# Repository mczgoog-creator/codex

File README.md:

# DRV8701 双电机驱动板 · Rev B

**12 V、39×60 mm、4 层、1.6 mm** 双电机驱动板。Rev B 重新安排了两路半桥、去耦和功率回路，并加入 TPS25910 主电源控制。每段线路、过孔和铜区均按明确坐标人工规划，未使用自动布线或路径搜索。

[网页端 KiCad 导入包](downloads/DRV8701_12V_KiCad5_Import.zip) · [完整工程和资料 ZIP](downloads/DRV8701_12V_EasyEDA_Pro.zip) · [工程说明](hardware/drv8701-dual-12v/README.md)

## 在嘉立创 EDA 专业版中打开

网页端请下载 **`DRV8701_12V_KiCad5_Import.zip`**，在开始页选择 **「导入 KiCad」**，直接选择 ZIP。按[官网指引](https://prodocs.lceda.cn/cn/import-export/import-kicad/index.html)，导入副本采用真实 KiCad 5.1 格式，并通过 KiCad 自带归档功能打包。步骤和导入后检查见[网页导入说明](hardware/drv8701-dual-12v/IMPORT_IN_WEB_PRO.md)。

原始 KiCad 9 工程和自带库也随包保存。`EasyEDA_Pro/DRV8701_DUAL_12V.eprj3` 是另供 V4.1+ 离线／半离线桌面客户端使用的文件夹工程；需保留整个目录，不能当作网页 `.epro` 文件导入。

## 本版变化

- 四组高边源极与低边漏极相邻，通过局部宽铜连接相节点；功率转层采用四孔阵列。公共供电在 C15 正极处汇合并向两路分配。
- 泵和内部电源去耦至芯片的关键连接留在顶层；VM 先到 C3/C10，再到芯片 VM 脚。SH 源参考采用独立细线返回高边源极焊盘。
- 新增 U6 TPS25910、SW1 和五个配套无源件。SW1 控制主电源，原 U5 继续控制 DRV8701 的 nSLEEP。原 38 个元件的取值保留；原有脚网络仅 P2.1 从 VM 改为新增电源入口 VM_RAW。

主电源连续额定 5 A，R12=40.2 kΩ 对应手册限流 4.5–5.5 A。主开关关闭时芯片仍消耗约 2.5 mA 典型／4 mA 最大，分压另约 90 µA；不提供电池物理隔离或反向电流阻断。开启主电源前应保持两路桥关闭，VM 稳定后再使能，详见[首次上电步骤](hardware/drv8701-dual-12v/FIRST_POWER_ON.md)。

## 文件与检查边界

- [原理图 PDF](hardware/drv8701-dual-12v/DRV8701_DUAL_12V_schematic.pdf)、[PCB 各层检查图](hardware/drv8701-dual-12v/PCB_layers_review.pdf)
- [元件清单](hardware/drv8701-dual-12v/components.csv)、[采购约束](hardware/drv8701-dual-12v/procurement_notes.csv)
- [布局与电流路径说明](hardware/drv8701-dual-12v/source/engineering_review.md)、[主电源手册核对](hardware/drv8701-dual-12v/source/tps25910_power_control_review.md)
- [原图保留范围核对](hardware/drv8701-dual-12v/validation/rev_b_original_source_contract.json)、[交付检查记录](hardware/drv8701-dual-12v/validation/final_delivery.json)
- [独立布局几何检查](hardware/drv8701-dual-12v/validation/layout_geometry_audit.json)、[最后丝印与铜线复核](hardware/drv8701-dual-12v/validation/rev_b_final_silk_cleanup.json)、[Rev B 工程审计](hardware/drv8701-dual-12v/validation/rev_b_engineering_audit.json)

Rev B 共 **45 个元件、38 个网络、203 个唯一物理引脚／211 个焊盘实例、592 段线路、151 个过孔、12 个铜区**。冻结后的 KiCad 9 源板 **DRC 0 违规／0 未连接，原理图 ERC 0 错误／0 警告**。独立几何检查通过：14 条关键去耦连接均在顶层，最长 2.9713 mm；丝印与焊盘／过孔碰撞为 0，审核范围内的直角／锐角弯折为 0。

网页导入副本已通过真实 **KiCad 5.1.9：ERC 0 错误／0 警告，PCB DRC 0 错误／0 未连接**；45 个元件、38 网、203 脚逐值逐脚一致。PCB 检查已重填全部铜区并检查走线与填铜。副本的 624 段线路中，新增 32 段完全位于原 MOS 漏极焊盘铜内，新增实际铜面积为 0；原 592 段线路、151 孔、211 焊盘及 12 铜区保留。见[旧版最终等价核对](hardware/drv8701-dual-12v/validation/legacy5_final_pcb_equivalence.json)。

源软件检查不替代专业版实际导入检查。弯折统计排除同网焊盘／过孔内部和真实分支结点，具体范围见几何报告。五页 PCB 检查图、分层 PDF 及顶／底 SVG／PNG 均按冻结源板重新导出，来源 SHA 见[预览导出记录](hardware/drv8701-dual-12v/validation/preview_exports.json)。

桌面原生工程的[静态转换审计](hardware/drv8701-dual-12v/EasyEDA_Pro/native-final-audit.json) 已通过：元件／引脚／线路／过孔及 12 个填充铜区均与冻结源板对应，官方工程结构检查 0 错误／0 警告。未运行真实专业版桌面客户端，网页用户仍使用上面的 KiCad 导入 ZIP。

**真实嘉立创网页导入／DRC、样板通电和温升测试尚未完成。** 导入会重新铺铜，需复核四层各 35 µm 铜、功率铜区和规则。原图的 100 nF 电荷泵／内部电源去耦、较弱齐纳供电、IDRIVE 设置和无 GND 的控制插座仍保留，并在工程说明中列出。MOS 原厂手册已读取，采购需匹配普通 SOP Advance 封装；手册没有提供推荐 PCB 焊盘图。

## 来源与许可证

官方开源转换／校验工具保留各自的 Apache-2.0／MIT 许可证；上游地址与精确版本见[版本记录](hardware/drv8701-dual-12v/tools/easyeda-native/upstream-versions.json)。这些工具许可证不自动覆盖电路设计、第三方封装或厂商 PDF。原图、封装和手册来源见工程说明。

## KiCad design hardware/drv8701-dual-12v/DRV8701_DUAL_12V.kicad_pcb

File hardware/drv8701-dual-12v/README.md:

# DRV8701 双电机驱动板 · Rev B · 12 V

依据用户原始《8701驱动板（无电流检测2.0）.pdf》重建。本版重新安排半桥功率器件、去耦、供电和回流，并按用户后续要求加入主电源控制。**原 38 个元件的取值全部保留；原有引脚唯一授权网络变化是 P2.1 从 VM 改接 VM_RAW。** 原图其余连接保留，新增七件：U6、SW1、R10–R12、C18、C19。核对见 [rev_b_original_source_contract.json](validation/rev_b_original_source_contract.json)。

PCB 每个元件位置、线路、过孔和铜区边界均人工规划，未使用嘉立创自动布线器、其它自动布线器或路径搜索。脚本按明确坐标生成线路；铺铜填充只是按既定边界生成铜区。

## 打开工程与交付文件

用户使用嘉立创 EDA 专业版**网页端**。主要入口为 **`DRV8701_12V_KiCad5_Import.zip`**：在网页开始页选择 **「导入 KiCad」**后直接选择 ZIP。依据[官网指引](https://prodocs.lceda.cn/cn/import-export/import-kicad/index.html)，导入副本采用真实 KiCad 5.1 格式并由 KiCad 自带归档功能打包。步骤见 [IMPORT_IN_WEB_PRO.md](IMPORT_IN_WEB_PRO.md)。

原始 KiCad 9 源文件与库保留。桌面入口 `EasyEDA_Pro/DRV8701_DUAL_12V.eprj3` 由官方转换器及独立后处理生成，另供专业版 V4.1+ 离线／半离线客户端使用，需保留整个目录；不能当作网页 `.epro` 文件导入。

**尚未在真实嘉立创 EDA 专业版完成导入和 DRC。** 导入会重建铜区，需复核板框、叠层、功率铜区和设计规则。桌面文件的 schema／真实导出模板单位差异见 `tools/easyeda-native/RESEARCH.md`；首次打开应确认实际尺寸和规则值。

|文件|用途|
|---|---|
|`DRV8701_DUAL_12V.kicad_sch/.kicad_pcb/.kicad_pro`|Rev B 可编辑原理图、PCB、规则|
|`DRV8701_Custom.kicad_sym`、`DRV8701_Custom.pretty/`|本地符号及封装；配套库表同目录保存|
|`KiCad_Import_5/`|真实 KiCad 5.1 格式的网页导入副本|
|`imports/DRV8701_12V_KiCad5_Import.zip`|专用网页导入 ZIP|
|`EasyEDA_Pro/`|另供新版桌面客户端使用的文件夹原生工程|
|`DRV8701_DUAL_12V_schematic.pdf`|原理图阅读版|
|`PCB_layers_review.pdf`、`pcb_top/bottom.svg/.png`|从源 CAD 导出的各层检查图与顶底预览；底层 PNG/SVG 已镜像，按从底面观察显示|
|`components.csv`、`procurement_notes.csv`|元件值、封装及采购额定参数|
|`source/source_netlist.json`|原始 PDF 独立复核网表，作为原图基准保留|
|`validation/rev_b_original_source_contract.json`|原图取值、连接与授权主电源差异核对|
|`final_drc.json`、`validation/schematic_erc.json`|冻结后的 KiCad 9 DRC 与原理图 ERC|
|`validation/layout_geometry_audit.json`|独立读取实际 PCB 的路径、弯折、过孔与丝印检查|
|`validation/rev_b_final_silk_cleanup.json`|最终丝印调整与唯一最后铜线修改范围|
|`validation/rev_b_engineering_audit.json`|本版功率网络、填铜与工程审计|
|`validation/preview_exports.json`|本版预览与各层 PDF 的源板 SHA／导出记录|
|`source/engineering_review.md`|本版布局与电流路径说明|
|`source/tps25910_power_control_review.md`|主电源芯片手册、启动／限流／关闭状态核对|
|`FIRST_POWER_ON.md`|首次上电和两级开关操作步骤|
|`footprint_geometry.json`、`manual_routes.json`|封装依据及人工规划线路记录|
|`scripts/generate_schematic.py`、`tools/build_board.py`|原理图及明确坐标的 PCB 生成程序|
|`validation/`|本版最终检查记录|

用 KiCad 9 打开 `.kicad_pro` 即可读取同目录库。重建程序会覆盖其负责的设计文件，运行前应保存手工编辑副本。

## 尺寸、电流与布局

仅采用用户电机表格的 **12 V** 条件：每路较高档额定 0.4 A、堵转 1.8 A；电机路径按每路 1.8 A，公共供电／回流按合计 3.6 A 规划。堵转值用于短时最大电流初筛，不表示允许持续堵转。

本版 **39×60 mm、4 层、标称 1.6 mm**，元件全在顶面。四铜层均 **35 µm（1 oz）**，孔电阻计算假设成品孔铜至少 20 µm。名义叠层：两面阻焊各 0.01 mm、四铜层各 0.035 mm、两段半固化片各 0.20 mm、中芯板 1.04 mm，总厚 1.60 mm；板厂应据实际材料匹配成品规格。普通 R/C/LED 为 0603，R8/R9 为 1210，新增 C18 为 0805；没有小于 0402 的贴片。

|通路|本版设计|
|---|---|
|P2 至 U6、U6 至 C15 及两路主供电|外层公共主干 1.80 mm；C15 正极为汇合与分配点|
|In2.Cu 并行供电|4.6 mm VM 公共铜带与局部宽铜支路|
|高边 MOS 漏极|短 1.0 mm 外层支路，并由内层铜和四孔阵列连接裸露漏极焊盘|
|高边源极至低边漏极|相邻封装间的局部顶层宽铜，四组半桥均按相同结构安排|
|电机连接器|0.70 mm 外层主线，每个相节点配四孔功率阵列|
|低边 MOS 源极|短支线接本地宽铜，四孔阵列接地；F.Cu／In1.Cu／B.Cu 地铜提供并行回流|
|U6 IN／OUT|各三个并联引脚，每脚短 0.45 mm 连接接入公共铜；不是单根 0.45 mm 线路承担 3.6 A|
|信号与驱动支路|约 0.20–0.30 mm；这些线路不承担电机主电流|

IPC-2221 经验式 `I=k×ΔT^0.44×A^0.725`（A 为平方 mil）用于初筛。35 µm 铜、约 10°C 温升时，外层 1.8 A／3.6 A 线宽约 0.676／1.758 mm，内层约 1.76／4.57 mm，因此内层公共 VM 铜带取 4.6 mm。该经验式不计算实际板上的电流密度、开关波形或温升，成品仍需测量。

C15 安排在受控 VM 供电汇合处，两路从其正极向外分配。每组高／低边 MOS 旋转后令高边源极紧邻低边裸露漏极，以宽铜连接相节点。泵／内部电源去耦至芯片的关键连接留在顶层，VM 电源先进入 C3/C10 再到 VM 引脚；C4/C11 位于功率母线旁。SH 源参考采用独立细线返回高边源极焊盘，但栅极和参考线仍有转层，14 条关键连接静态路径的最大长度为 2.9713 mm、0 转层；GH1 约 19.22 mm、GH2 约 13.56 mm 且仍有转层，不能宣称全部驱动回路已最小化或开关振铃已验证。

制造规则最小间距／线宽 0.15 mm，普通信号孔 0.45/0.20 mm，最小钻孔 0.20 mm、最小环宽 0.10 mm。具体功率孔阵列和最终几何以本版检查报告为准。

## 主电源与接口

|位号|功能与引脚|
|---|---|
|P2|12 V 电源 XT30：1=VM_RAW 正极，2=GND|
|U6|TPS25910RSAR：IN 1/2/3=VM_RAW；OUT 10/11/12=VM；中心焊盘接 GND|
|SW1|主电源开关：2=PWR_EN，3=GND，1=NC；接通 2–3 时 U6 导通|
|U5|原 DRV8701 使能：2=NSLEEP，3=齐纳 3V3，1=NC；断开 2–3 时为休眠档|
|CN1/CN2|左／右电机 XT30：1=L_A/R_A，2=L_B/R_B|
|CN3|1=R_EN，2=R_PH，3=L_PH，4=L_EN；原图未设置 GND 引脚|

CN3 没有公共地针脚，控制器 GND 必须另外连接 P2 的 GND。SW1 是主供电控制，U5 是驱动芯片睡眠控制，二者不能混用。

TPS25910 工作电压 3–20 V、IN/OUT 绝对最大 22 V；本工程仅按 12 V 使用。连续额定 5 A，R12=40.2 kΩ、1% 对应限流 **4.5 A 最小／5 A 典型／5.5 A 最大**。这只是公共电源故障控制，不是两路电机各自的电流测量或斩波限流。3.6 A 时芯片导通损耗约 0.38 W 典型／0.54 W 最大，需要焊实中心接地焊盘并验证温升。

EN 为低电平有效。SW1 接通将 EN 拉地；断开时 R10=100 kΩ、R11=33 kΩ 分压产生约 2.98 V 高电平关闭。**关闭时 U6 自身仍消耗 2.5 mA 典型／4 mA 最大，分压另约 90 µA**。C15 储能和电机回馈可能使 VM 暂时有电；TPS25910 本身没有反向电流阻断，因此主开关不是电池物理隔离。长期存放应拔掉电源。

C19=10 nF 对 12 V 的理想上升时间约 **11.1 ms 典型**，按手册 8–15 µA 驱动电流初算约 **8.2–15.3 ms**。实际电容、输入电源、限流和热保护会改变或延长启动。手册 12 V 启动最小负载电阻为 12 Ω，接有 C15 时可用启动负载进一步减少；因此**开启 SW1 前保持 U5 休眠并令两路 EN=0，VM 稳定后再使能电机**。不得把典型上升时间当作控制器等待的保证值。

## PWM 与原图保留问题

按用户确认的 **不高于 20 kHz EN PWM** 使用，PH 固定方向。R8/R9=100 Ω、C16/C17=100 nF 串联 RC 保留；电阻采用 **1210、至少 0.5 W**。12 V／20 kHz 充分充放电模型每路约 0.288 W 上界、50% 占空比约 0.244 W。PH 周期翻转会产生更大的跨端阶跃，不能沿用该热假设。

|项目|保留的原图与影响|
|---|---|
|C2/C9 VCP–VM|100 nF，TI 推荐 1 µF；须检查泵纹波与驱动欠压|
|C5/C12 AVDD、C6/C13 DVDD|100 nF，TI 推荐 1 µF；须核查 LDO 稳定性和纹波|
|C1/C8 CPH–CPL|100 nF，与 TI 推荐值一致|
|VM 旁路|保留 100 nF 与公共 C15=470 µF；须测供电／再生电压|
|VREF／IDRIVE|各自接 AVDD；约 25/50 mA 源／灌，关闭高边 VDS 过流检测|
|SP／SN|接 GND；没有电机电流采样及各路可设斩波限流|
|nFAULT／SNSOUT／SO|原图 NC，控制器不能由这些脚接收原驱动器故障或采样信息|
|10 kΩ／齐纳 3V3|12 V 下假定 3.3 V 时总馈电约 0.87 mA；还供 LED 与 nSLEEP，须实测低电流工作点|
|CN3|无 GND 引脚，控制器另行共地|

布局重排和新增主开关没有修正上述原值与原连接。首次验证内容及顺序见 [FIRST_POWER_ON.md](FIRST_POWER_ON.md)。

## 焊接与采购复核

DRV8701 是 4×4 mm RGE24 VQFN、0.5 mm 脚距，中心地焊盘必须焊实。U6 是带中心地焊盘的 RSA16 VQFN。建议焊膏、预热和热风／手动回流；仅烙铁处理外围脚不能保证中心焊接。未填孔热过孔会吸锡，需检查浮高和空洞。

TPH1R403NL：1/2/3=S、4=G、5/6/7/8=D，中心裸露金属同属 D；高边裸露焊盘为 VM，低边为相节点，不能当作接地散热焊盘。原厂 **2026-04-14 Rev.3.0.A** 已读取：VDS 30 V、VGS ±20 V；10 V 下 RDS(on) 典型 1.2 mΩ／最大 1.4 mΩ，Qg 典型 46 nC、Qgd 典型 4.3 nC。引脚与普通 SOP Advance 的机械图已核对，详见 [原厂核对](source/tph1r403nl_manufacturer_review.md)。

该手册 p8 普通 SOP Advance 与 p9 SOP Advance(N) 不同，采购需匹配 p8。手册未提供推荐 PCB 铜焊盘图，外围 0.5×1.2 mm 焊盘是本设计尺寸。典型 Qg／原图 25/50 mA 的估算不替代最坏公差及实测 VGS。

SS12D10G4 的用户实测脚宽 1.3 mm、厚 0.8 mm，使用 2.3×1.1 mm 槽孔。C18 采购目标为 4.7 µF／50 V／X7R／0805，**须按具体料号的 DC 偏压曲线核对 12 V 下有效电容≥1 µF**；当前没有对某个采购料号完成该曲线验证。XT30、XH 实物外形、极性与 U6 钢网要求也应按采购品及厂商图复核。

## 来源与验证边界

- 原始 PDF：用户提供，见 `source/original_schematic.pdf`；原始网表见 `source/source_netlist.json`。
- TI DRV8701：[原厂手册](https://www.ti.com/lit/ds/symlink/drv8701.pdf)，SLVSCX5B，附原厂镜像 PDF `source/TI_DRV8701_SLVSCX5B.pdf`；镜像来自 [Tinkerforge](https://github.com/Tinkerforge/performance-dc-bricklet/blob/master/datasheets/drv8701.pdf)。
- TI TPS25910：`source/TI_TPS25910_SLUSAR6D.pdf` 与 EVM 手册；参数、封装及页码见 [主电源核对](source/tps25910_power_control_review.md)。
- Toshiba：[精确型号原厂 PDF](https://toshiba.semicon-storage.com/info/TPH1R403NL_datasheet_en_20191030.pdf?did=14296&prodName=TPH1R403NL)，本包为 Rev.3.0.A；MOS 封装几何另参考 [zdxddmx/smartcar-hardware](https://github.com/zdxddmx/smartcar-hardware) 的同型号原生库，交叉核对 [CaptainJaja/DRV8701_2Motors](https://github.com/CaptainJaja/DRV8701_2Motors)。未复用其它工程的 PCB 布局或布线。
- 官方转换／验证工具保留原许可证，上游 URL／commit 见 `tools/easyeda-native/upstream-versions.json`。

本版为 **45 个元件、38 个网络、203 个唯一物理引脚／211 个焊盘实例**，592 段人工指定线路、151 个过孔、12 个铜区。源 KiCad 9、KiCad 5 导入副本和桌面原生工程分别核对，各自结果保存于 `validation/`、`KiCad_Import_5/validation/` 和 `EasyEDA_Pro/native-*.json`，不沿用 Rev A 检查成绩。

冻结后的源板 KiCad 9 **DRC 0 违规、0 未连接**，原理图 **ERC 0 错误、0 警告**。独立 [布局几何审计](validation/layout_geometry_audit.json) 通过，14 条关键去耦连接全部顶层且 0 转层，最长 2.9713 mm；丝印与焊盘／过孔碰撞 0，审核范围内直角／锐角弯折 0。弯折分类排除同网焊盘／过孔内以及真实分支结点。最终 PCB SHA256 为 `daa3c5be68e8667a06f6da7ec5fd3c1238de758fb6982bcae6e130e6b8204989`。

[最终丝印复核](validation/rev_b_final_silk_cleanup.json) 确认最后铜修改仅把 C18.1 至 U6 IN 汇流处的一段 VM_RAW 输入颈缩由 0.9 mm 加宽到 1.8 mm；其它焊盘、过孔和铜区边界未在该步骤改变。R10 位号移至底层，其余位号在顶层；主电源／休眠开关说明与板名位于背面，开关 ON 仍对应右侧／pin3。功率铜区和原图差异另见 [Rev B 工程审计](validation/rev_b_engineering_audit.json)。

桌面原生工程 [native-final-audit.json](EasyEDA_Pro/native-final-audit.json) 已通过静态转换检查，源板 SHA 与冻结文件一致。45 件／38 网／203 个唯一脚、592 段线路、151 孔及 12 个实际填充铜区逐项对应；四层、叠层厚度、区优先级及直接焊盘连接参数保留。格式检查 4096 条外层记录有效，未映射类型／未解释失败均为 0；已知 schema 与真实导出差异单列，官方工程结构检查 0 错误／0 警告。**这些是文件级检查，实际专业版桌面打开与 DRC 未执行。**

网页副本已由真实 **KiCad 5.1.9** 检查：原理图 **ERC 0 错误／0 警告**，PCB **DRC 0 错误／0 未连接**。检查已重填全部铜区，并开启全部走线错误及走线与填铜检查。45 件及原值、38 网、203 个唯一脚（194 连接、9 NC）逐项一致。副本保留源板 592 段线路、151 孔、211 焊盘和 12 铜区，另加 32 段完全在 MOS 既有漏极焊盘铜内的连接段，使旧版识别原有铜连通；副本共 624 段、新增实际铜面积 **0.0 mm²**。新旧填铜缓存随软件版本不同，按源区边界／参数在旧版实际重填；审计见 [legacy5_final_pcb_equivalence.json](validation/legacy5_final_pcb_equivalence.json)。

原理图 PDF、五页 PCB 各层检查 PDF、各层独立 PDF 与顶／底 SVG／PNG 均已更新为冻结 Rev B，源板 SHA 与导出方式见 [preview_exports.json](validation/preview_exports.json)。底层预览已镜像；层 PDF 由源 CAD SVG 经矢量转换生成，以保留完整板框。

本交付没有生产下单或 Gerber 制造放行。**真实专业版导入、铺铜／DRC，以及样板启动、开关波形、温升和短时堵转测试未完成。** 静态格式或铜几何核对不能代替这些实测。

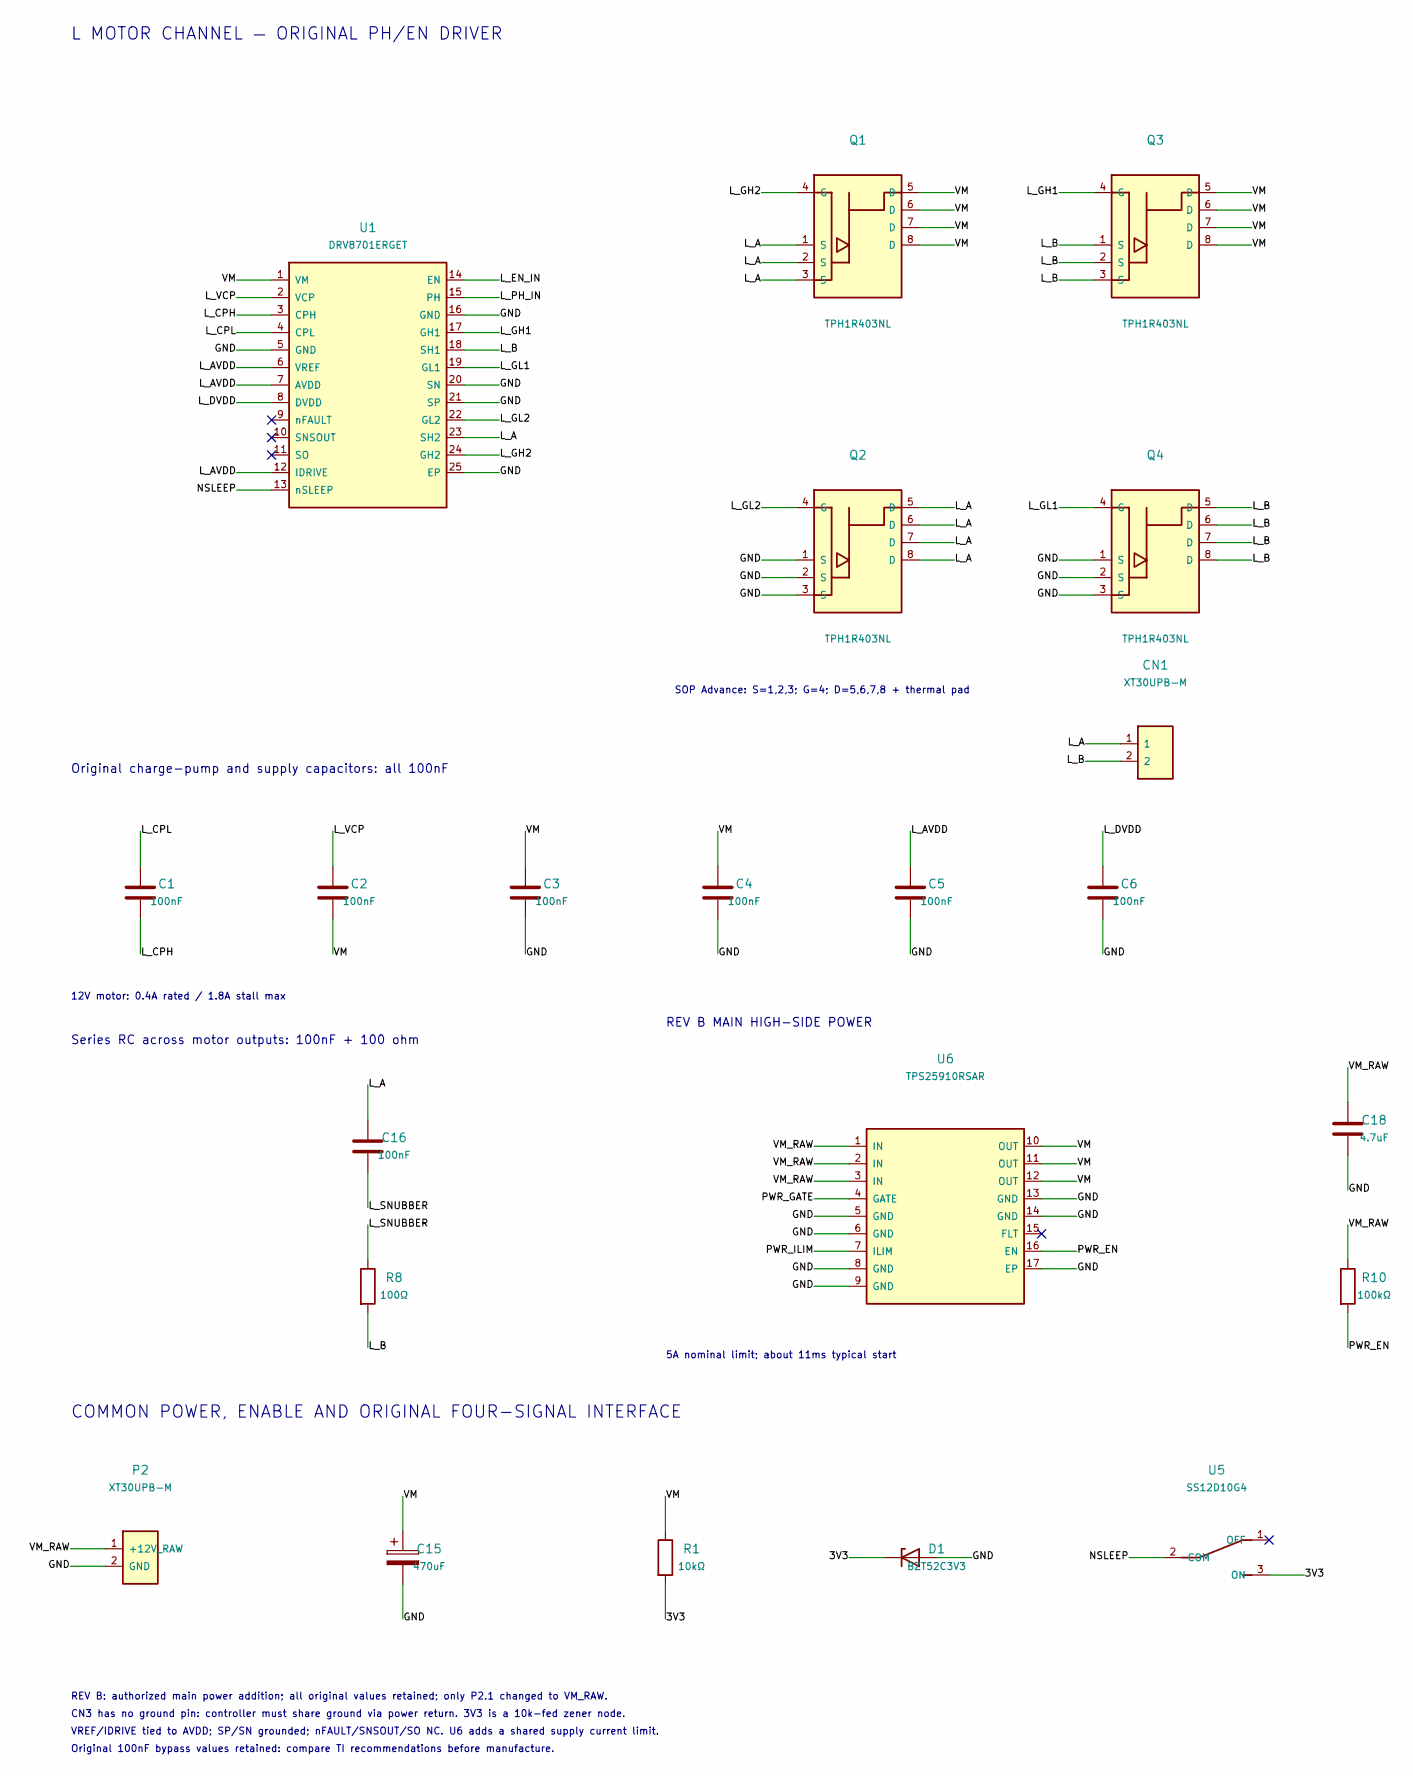
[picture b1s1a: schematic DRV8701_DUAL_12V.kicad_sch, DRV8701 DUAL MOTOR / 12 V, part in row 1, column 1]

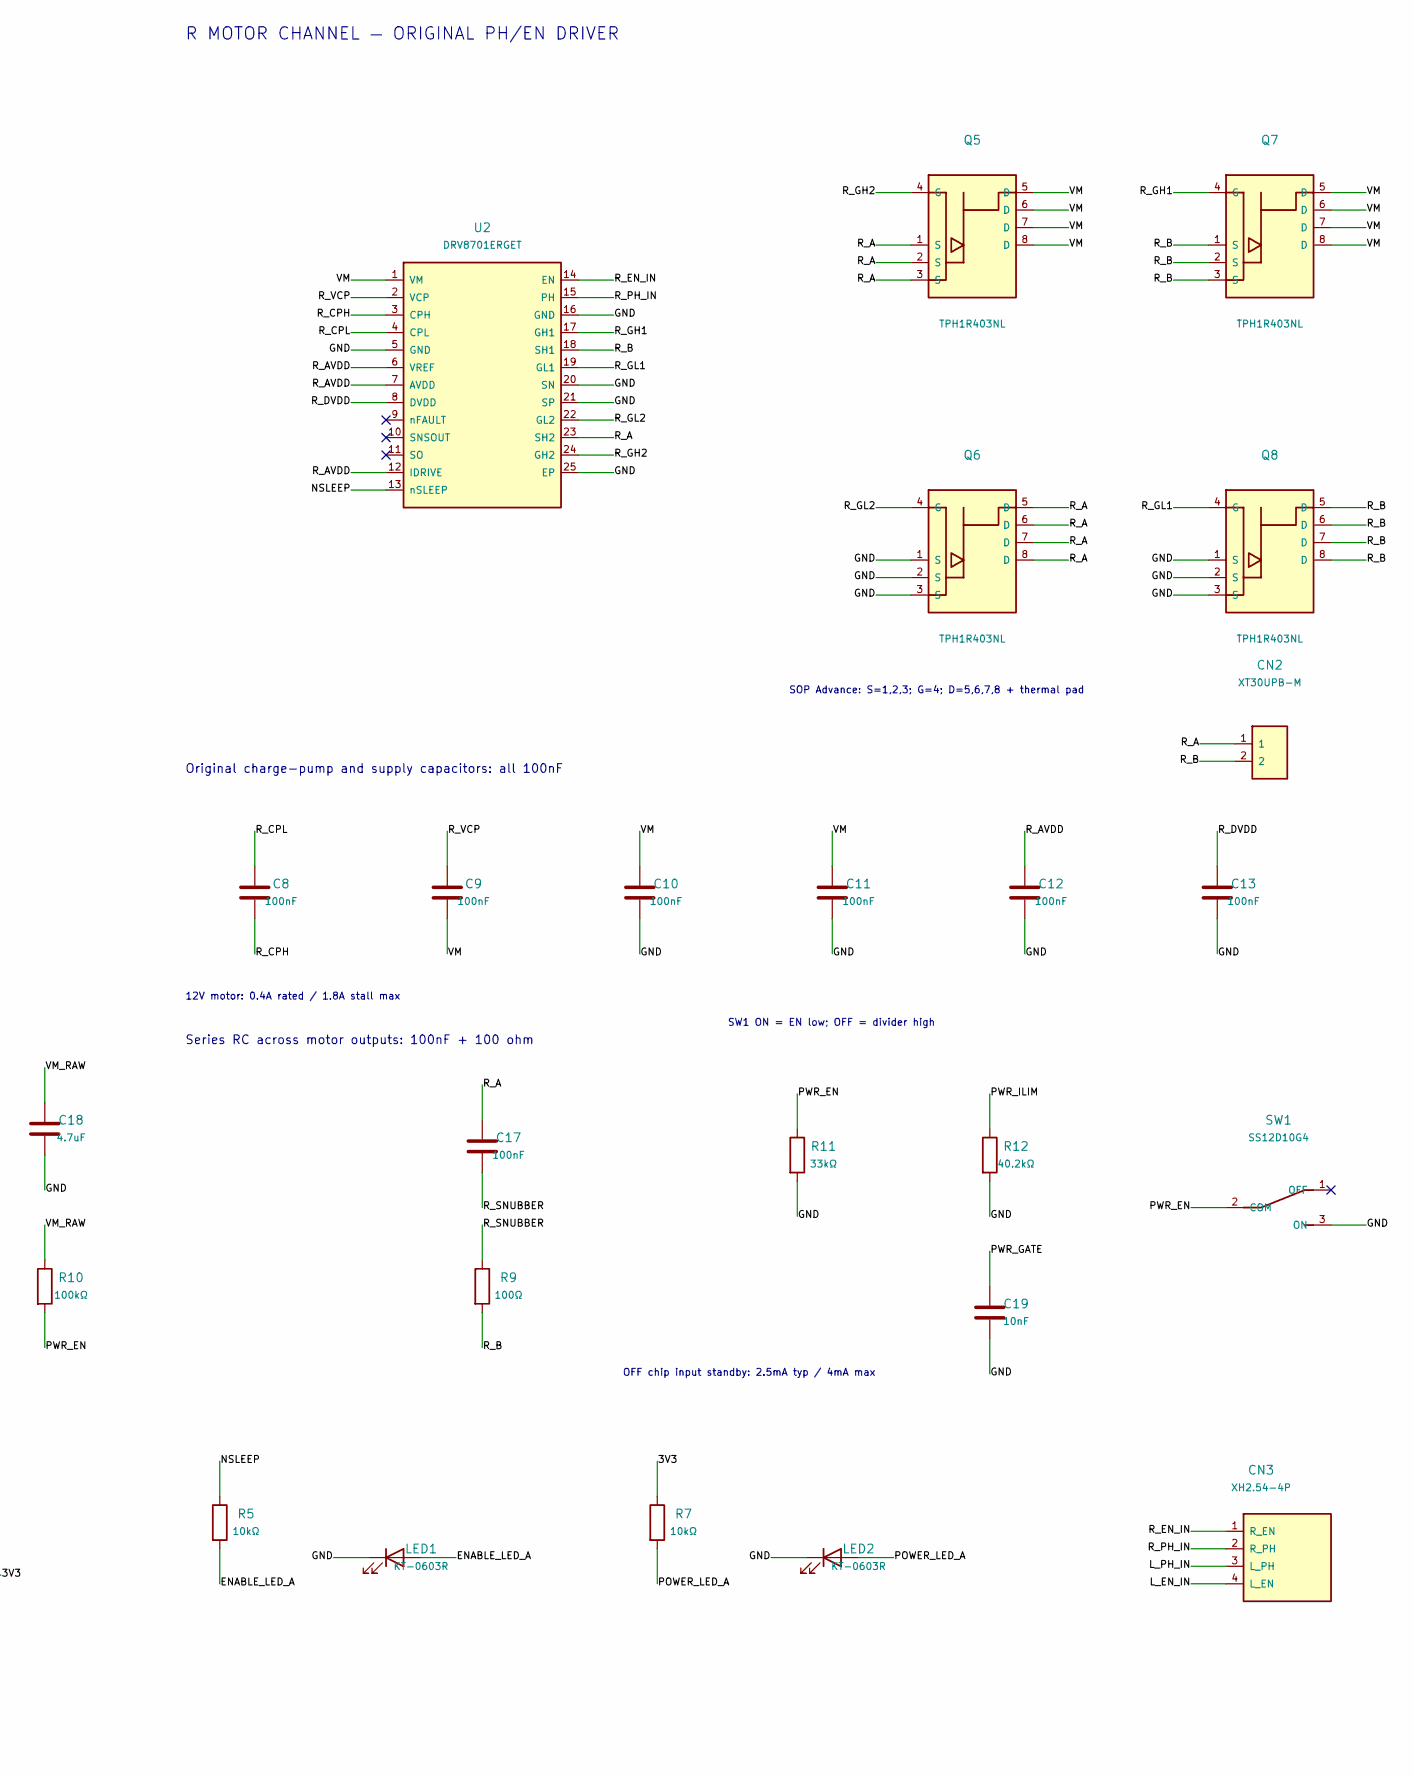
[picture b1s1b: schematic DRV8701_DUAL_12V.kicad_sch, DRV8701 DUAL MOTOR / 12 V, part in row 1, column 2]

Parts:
C1, C2, C3, C4, C5, C6, C8, C9, C10, C11, C12, C13, C16, C17: 100nF; C_0603_1608Metric
C15: 470uF; CP_Radial_D10.0mm_P5.00mm
C18: 4.7uF; C_0805_2012Metric
C19: 10nF; C_0603_1608Metric
CN1, CN2: XT30UPB-M; AMASS_XT30UPB_M_SourceNumbering
CN3: XH2.54-4P; XH2.54_1x04_Vertical
D1: BZT52C3V3; D_SOD123
LED1, LED2: KT-0603R; LED_0603_1608Metric
P2: XT30UPB-M; AMASS_XT30UPB_M_SourceNumbering
Q1, Q2, Q3, Q4, Q5, Q6, Q7, Q8: TPH1R403NL; TPH1R403NL_SOPAdvance
R1, R5, R7: 10kΩ; R_0603_1608Metric
R8, R9: 100Ω; R_1210_3225Metric
R10: 100kΩ; R_0603_1608Metric
R11: 33kΩ; R_0603_1608Metric
R12: 40.2kΩ; R_0603_1608Metric
SW1: SS12D10G4
U1, U2: DRV8701ERGET; DRV8701_RGE24
U5: SS12D10G4
U6: TPS25910RSAR; TPS25910_RSA16

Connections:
3V3: D1.1 (K), R1.2, R7.1, U5.3 (ON)
ENABLE_LED_A: LED1.2 (A), R5.2
GND: C3.2, C4.2, C5.2, C6.2, C10.2, C11.2, C12.2, C13.2, C15.2, C18.2, C19.2, D1.2 (A), LED1.1 (K), LED2.1 (K), P2.2 (GND), Q2.1 (S), Q2.2 (S), Q2.3 (S), Q4.1 (S), Q4.2 (S), Q4.3 (S), Q6.1 (S), Q6.2 (S), Q6.3 (S), Q8.1 (S), Q8.2 (S), Q8.3 (S), R11.2, R12.2, SW1.3 (ON), U1.5 (GND), U1.16 (GND), U1.20 (SN), U1.21 (SP), U1.25 (EP), U2.5 (GND), U2.16 (GND), U2.20 (SN), U2.21 (SP), U2.25 (EP), U6.5 (GND), U6.6 (GND), U6.8 (GND), U6.9 (GND), U6.13 (GND), U6.14 (GND), U6.17 (EP)
L_A: C16.1, CN1.1, Q1.1 (S), Q1.2 (S), Q1.3 (S), Q2.5 (D), Q2.6 (D), Q2.7 (D), Q2.8 (D), U1.23 (SH2)
L_AVDD: C5.1, U1.6 (VREF), U1.7 (AVDD), U1.12 (IDRIVE)
L_B: CN1.2, Q3.1 (S), Q3.2 (S), Q3.3 (S), Q4.5 (D), Q4.6 (D), Q4.7 (D), Q4.8 (D), R8.2, U1.18 (SH1)
L_CPH: C1.2, U1.3 (CPH)
L_CPL: C1.1, U1.4 (CPL)
L_DVDD: C6.1, U1.8 (DVDD)
L_EN_IN: CN3.4 (L_EN), U1.14 (EN)
L_GH1: Q3.4 (G), U1.17 (GH1)
L_GH2: Q1.4 (G), U1.24 (GH2)
L_GL1: Q4.4 (G), U1.19 (GL1)
L_GL2: Q2.4 (G), U1.22 (GL2)
L_PH_IN: CN3.3 (L_PH), U1.15 (PH)
L_SNUBBER: C16.2, R8.1
L_VCP: C2.1, U1.2 (VCP)
NSLEEP: R5.1, U1.13 (nSLEEP), U2.13 (nSLEEP), U5.2 (COM)
POWER_LED_A: LED2.2 (A), R7.2
PWR_EN: R10.2, R11.1, SW1.2 (COM), U6.16 (EN)
PWR_GATE: C19.1, U6.4 (GATE)
PWR_ILIM: R12.1, U6.7 (ILIM)
R_A: C17.1, CN2.1, Q5.1 (S), Q5.2 (S), Q5.3 (S), Q6.5 (D), Q6.6 (D), Q6.7 (D), Q6.8 (D), U2.23 (SH2)
R_AVDD: C12.1, U2.6 (VREF), U2.7 (AVDD), U2.12 (IDRIVE)
R_B: CN2.2, Q7.1 (S), Q7.2 (S), Q7.3 (S), Q8.5 (D), Q8.6 (D), Q8.7 (D), Q8.8 (D), R9.2, U2.18 (SH1)
R_CPH: C8.2, U2.3 (CPH)
R_CPL: C8.1, U2.4 (CPL)
R_DVDD: C13.1, U2.8 (DVDD)
R_EN_IN: CN3.1 (R_EN), U2.14 (EN)
R_GH1: Q7.4 (G), U2.17 (GH1)
R_GH2: Q5.4 (G), U2.24 (GH2)
R_GL1: Q8.4 (G), U2.19 (GL1)
R_GL2: Q6.4 (G), U2.22 (GL2)
R_PH_IN: CN3.2 (R_PH), U2.15 (PH)
R_SNUBBER: C17.2, R9.1
R_VCP: C9.1, U2.2 (VCP)
VM: C2.2, C3.1, C4.1, C9.2, C10.1, C11.1, C15.1, Q1.5 (D), Q1.6 (D), Q1.7 (D), Q1.8 (D), Q3.5 (D), Q3.6 (D), Q3.7 (D), Q3.8 (D), Q5.5 (D), Q5.6 (D), Q5.7 (D), Q5.8 (D), Q7.5 (D), Q7.6 (D), Q7.7 (D), Q7.8 (D), R1.1, U1.1 (VM), U2.1 (VM), U6.10 (OUT), U6.11 (OUT), U6.12 (OUT)
VM_RAW: C18.1, P2.1 (+12V_RAW), R10.1, U6.1 (IN), U6.2 (IN), U6.3 (IN)

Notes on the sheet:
L MOTOR CHANNEL — ORIGINAL PH/EN DRIVER
SOP Advance: S=1,2,3; G=4; D=5,6,7,8 + thermal pad
Original charge-pump and supply capacitors: all 100nF
Series RC across motor outputs: 100nF + 100 ohm
12V motor: 0.4A rated / 1.8A stall max
R MOTOR CHANNEL — ORIGINAL PH/EN DRIVER
REV B MAIN HIGH-SIDE POWER
SW1 ON = EN low; OFF = divider high
5A nominal limit; about 11ms typical start
OFF chip input standby: 2.5mA typ / 4mA max
COMMON POWER, ENABLE AND ORIGINAL FOUR-SIGNAL INTERFACE
REV B: authorized main power addition; all original values retained; only P2.1 changed to VM_RAW.
CN3 has no ground pin: controller must share ground via power return. 3V3 is a 10k-fed zener node.
VREF/IDRIVE tied to AVDD; SP/SN grounded; nFAULT/SNSOUT/SO NC. U6 adds a shared supply current limit.
Original 100nF bypass values retained: compare TI recommendations before manufacture.

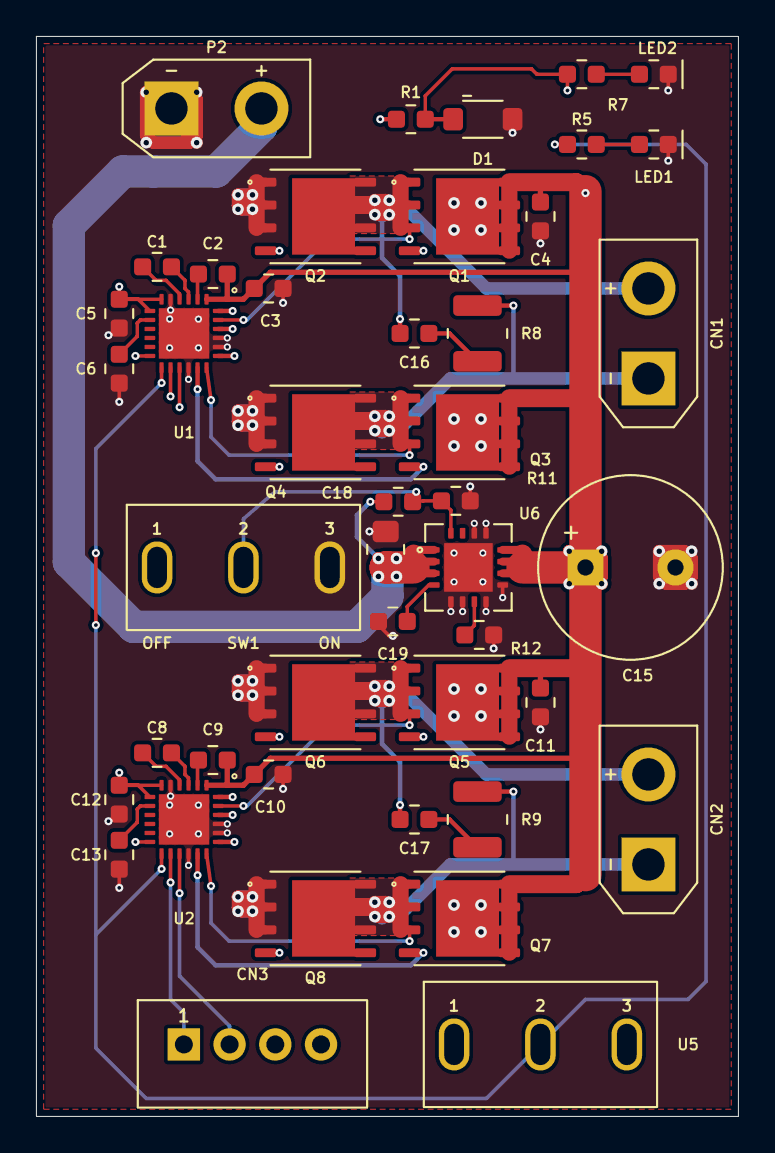
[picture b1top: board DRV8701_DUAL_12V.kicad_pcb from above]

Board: 4 copper layers, 39.0 x 60.0 mm, 45 parts (0 on the bottom side), 38 nets.

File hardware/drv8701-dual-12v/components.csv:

Reference,Value,Footprint,Quantity,PCB side,Source fidelity,Rating / tolerance
U1,DRV8701ERGET,DRV8701_Custom:DRV8701_RGE24,1,Front,Original value and connectivity,
Q1,TPH1R403NL,DRV8701_Custom:TPH1R403NL_SOPAdvance,1,Front,Original value and connectivity,
Q2,TPH1R403NL,DRV8701_Custom:TPH1R403NL_SOPAdvance,1,Front,Original value and connectivity,
Q3,TPH1R403NL,DRV8701_Custom:TPH1R403NL_SOPAdvance,1,Front,Original value and connectivity,
Q4,TPH1R403NL,DRV8701_Custom:TPH1R403NL_SOPAdvance,1,Front,Original value and connectivity,
C1,100nF,DRV8701_Custom:C_0603_1608Metric,1,Front,Original value and connectivity,
C2,100nF,DRV8701_Custom:C_0603_1608Metric,1,Front,Original value and connectivity,
C3,100nF,DRV8701_Custom:C_0603_1608Metric,1,Front,Original value and connectivity,
C4,100nF,DRV8701_Custom:C_0603_1608Metric,1,Front,Original value and connectivity,
C5,100nF,DRV8701_Custom:C_0603_1608Metric,1,Front,Original value and connectivity,
C6,100nF,DRV8701_Custom:C_0603_1608Metric,1,Front,Original value and connectivity,
C16,100nF,DRV8701_Custom:C_0603_1608Metric,1,Front,Original value and connectivity,
R8,100Ω,DRV8701_Custom:R_1210_3225Metric,1,Front,Original value and connectivity,
CN1,XT30UPB-M,DRV8701_Custom:AMASS_XT30UPB_M_SourceNumbering,1,Front,Original value and connectivity,
U2,DRV8701ERGET,DRV8701_Custom:DRV8701_RGE24,1,Front,Original value and connectivity,
Q5,TPH1R403NL,DRV8701_Custom:TPH1R403NL_SOPAdvance,1,Front,Original value and connectivity,
Q6,TPH1R403NL,DRV8701_Custom:TPH1R403NL_SOPAdvance,1,Front,Original value and connectivity,
Q7,TPH1R403NL,DRV8701_Custom:TPH1R403NL_SOPAdvance,1,Front,Original value and connectivity,
Q8,TPH1R403NL,DRV8701_Custom:TPH1R403NL_SOPAdvance,1,Front,Original value and connectivity,
C8,100nF,DRV8701_Custom:C_0603_1608Metric,1,Front,Original value and connectivity,
C9,100nF,DRV8701_Custom:C_0603_1608Metric,1,Front,Original value and connectivity,
C10,100nF,DRV8701_Custom:C_0603_1608Metric,1,Front,Original value and connectivity,
C11,100nF,DRV8701_Custom:C_0603_1608Metric,1,Front,Original value and connectivity,
C12,100nF,DRV8701_Custom:C_0603_1608Metric,1,Front,Original value and connectivity,
C13,100nF,DRV8701_Custom:C_0603_1608Metric,1,Front,Original value and connectivity,
C17,100nF,DRV8701_Custom:C_0603_1608Metric,1,Front,Original value and connectivity,
R9,100Ω,DRV8701_Custom:R_1210_3225Metric,1,Front,Original value and connectivity,
CN2,XT30UPB-M,DRV8701_Custom:AMASS_XT30UPB_M_SourceNumbering,1,Front,Original value and connectivity,
U6,TPS25910RSAR,DRV8701_Custom:TPS25910_RSA16,1,Front,Authorized Rev B addition,
C18,4.7uF,DRV8701_Custom:C_0805_2012Metric,1,Front,Authorized Rev B addition,50V X7R 0805; verify exact selected part effective capacitance >=1uF at 12V from manufacturer DC-bias curve
R10,100kΩ,DRV8701_Custom:R_0603_1608Metric,1,Front,Authorized Rev B addition,1%
R11,33kΩ,DRV8701_Custom:R_0603_1608Metric,1,Front,Authorized Rev B addition,1%
R12,40.2kΩ,DRV8701_Custom:R_0603_1608Metric,1,Front,Authorized Rev B addition,1%
C19,10nF,DRV8701_Custom:C_0603_1608Metric,1,Front,Authorized Rev B addition,50V C0G
SW1,SS12D10G4,DRV8701_Custom:SS12D10G4,1,Front,Authorized Rev B addition,
P2,XT30UPB-M,DRV8701_Custom:AMASS_XT30UPB_M_SourceNumbering,1,Front,Original value; authorized P2.1 net split,
C15,470uF,DRV8701_Custom:CP_Radial_D10.0mm_P5.00mm,1,Front,Original value and connectivity,
R1,10kΩ,DRV8701_Custom:R_0603_1608Metric,1,Front,Original value and connectivity,
D1,BZT52C3V3,DRV8701_Custom:D_SOD123,1,Front,Original value and connectivity,
U5,SS12D10G4,DRV8701_Custom:SS12D10G4,1,Front,Original value and connectivity,
R5,10kΩ,DRV8701_Custom:R_0603_1608Metric,1,Front,Original value and connectivity,
LED1,KT-0603R,DRV8701_Custom:LED_0603_1608Metric,1,Front,Original value and connectivity,
R7,10kΩ,DRV8701_Custom:R_0603_1608Metric,1,Front,Original value and connectivity,
LED2,KT-0603R,DRV8701_Custom:LED_0603_1608Metric,1,Front,Original value and connectivity,
CN3,XH2.54-4P,DRV8701_Custom:XH2.54_1x04_Vertical,1,Front,Original value and connectivity,

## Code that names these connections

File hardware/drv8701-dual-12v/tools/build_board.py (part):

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array('GND',(32.5,29.5),1.8)
# Raw input power uses the bottom LEFT edge; motor outputs occupy the right.
raw_sites=array('VM_RAW',(16.5,29.5),1.0)
route('VM_RAW',p.B_Cu,1.8,loc('P2',1),(9.5,5),(7,7.5),(3.5,7.5),(1.8,7.5),(-1.2,10.5),
      (-1.2,29.2),(2.4,32.8),(14.8,32.8),(16.5,31.1),(16.5,29.5))
route('VM_RAW',p.F_Cu,1.8,(16.5,29.5),loc('C18',1))
route('VM_RAW',p.F_Cu,1.8,loc('C18',1),(17.95,29.5))
for i in [1,2,3]:
    a=loc('U6',i)
    route('VM_RAW',p.F_Cu,.45,a,(18.2,a[1]),(17.95,a[1]+.25 if i==1 else a[1]-.25)) if i!=2 else route('VM_RAW',p.F_Cu,.45,a,(17.95,a[1]))
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    else:end=(a[0],a[1]-.55)
    route('GND',p.F_Cu,.2,a,end);via('GND',end,.4,.2)
escape('C18',2,(15.5,27.5))
route('PWR_GATE',p.F_Cu,.2,loc('U6',4),(18.8,30.475),(17.6,31.675),loc('C19',1))
route('GND',p.F_Cu,.2,loc('C19',2),(16,32.7),(16.6,33.3),(16.8,33.3));via('GND',(16.8,33.3))
route('PWR_ILIM',p.F_Cu,.2,loc('U6',7),(21.325,32.725),loc('R12',1))
escape('R12',2,(22.4,34))
escape('R11',2,(21.1,25.0))
route('PWR_EN',p.F_Cu,.2,loc('R10',2),(18.5,25.8),loc('R11',1))
route('PWR_EN',p.F_Cu,.2,loc('R11',1),(20.025,26.325),loc('U6',16))
e=escape('R10',2,(18.1,25.3))
route('PWR_EN',p.B_Cu,.2,loc('SW1',2),(8.5,26.8),(10.25,25.3),e)
escape('R10',1,(15.55,25.85))
route('VM_RAW',p.B_Cu,.25,(15.55,25.85),(14.8,26.6),(14.8,27.8),(16.5,29.5))

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a=escape('R7',1,(26.5,3))
route('3V3',p.In2_Cu,.2,a,(28.5,1),(34,1),(34.8,1.8),(34.8,52),(31.8,55),loc('U5',3))
a=escape('R5',1,(25.8,6))
route('NSLEEP',p.B_Cu,.2,a,(33.1,6),(34.2,7.1),(34.2,52.5),(33.2,53.5),(27.5,53.5),loc('U5',2))
route('NSLEEP',p.B_Cu,.2,(3.95,19.25),(.3,22.9),(.3,28.7))
via('NSLEEP',(.3,28.7));via('NSLEEP',(.3,32.7))
route('NSLEEP',p.F_Cu,.2,(.3,28.7),(.3,32.7))
route('NSLEEP',p.B_Cu,.2,(.3,32.7),(.3,56.2),(3.1,59),(22,59),loc('U5',2))
route('NSLEEP',p.B_Cu,.2,(3.95,46.25),(.3,49.9))
route('L_EN_IN',p.In2_Cu,.2,(4.45,20),(-2,26.45),(-2,53),(3.2,58.2),(12.2,58.2),(12.81,57.59),loc('CN3',4))
route('L_PH_IN',p.In2_Cu,.2,(4.95,20.6),(-.5,26.05),(-.5,49.77),(3.73,54),(8.27,54),loc('CN3',3))
route('R_EN_IN',p.B_Cu,.2,(4.45,47),(4.45,53.5),(5.19,54.24),loc('CN3',1))
route('R_PH_IN',p.B_Cu,.2,(4.95,47.6),(4.95,52.2),(7.73,54.98),loc('CN3',2))

# Outline and reference text are designed independently of component orientation.
# The QFN top corners in the library conflict with the adjacent, intentionally
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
